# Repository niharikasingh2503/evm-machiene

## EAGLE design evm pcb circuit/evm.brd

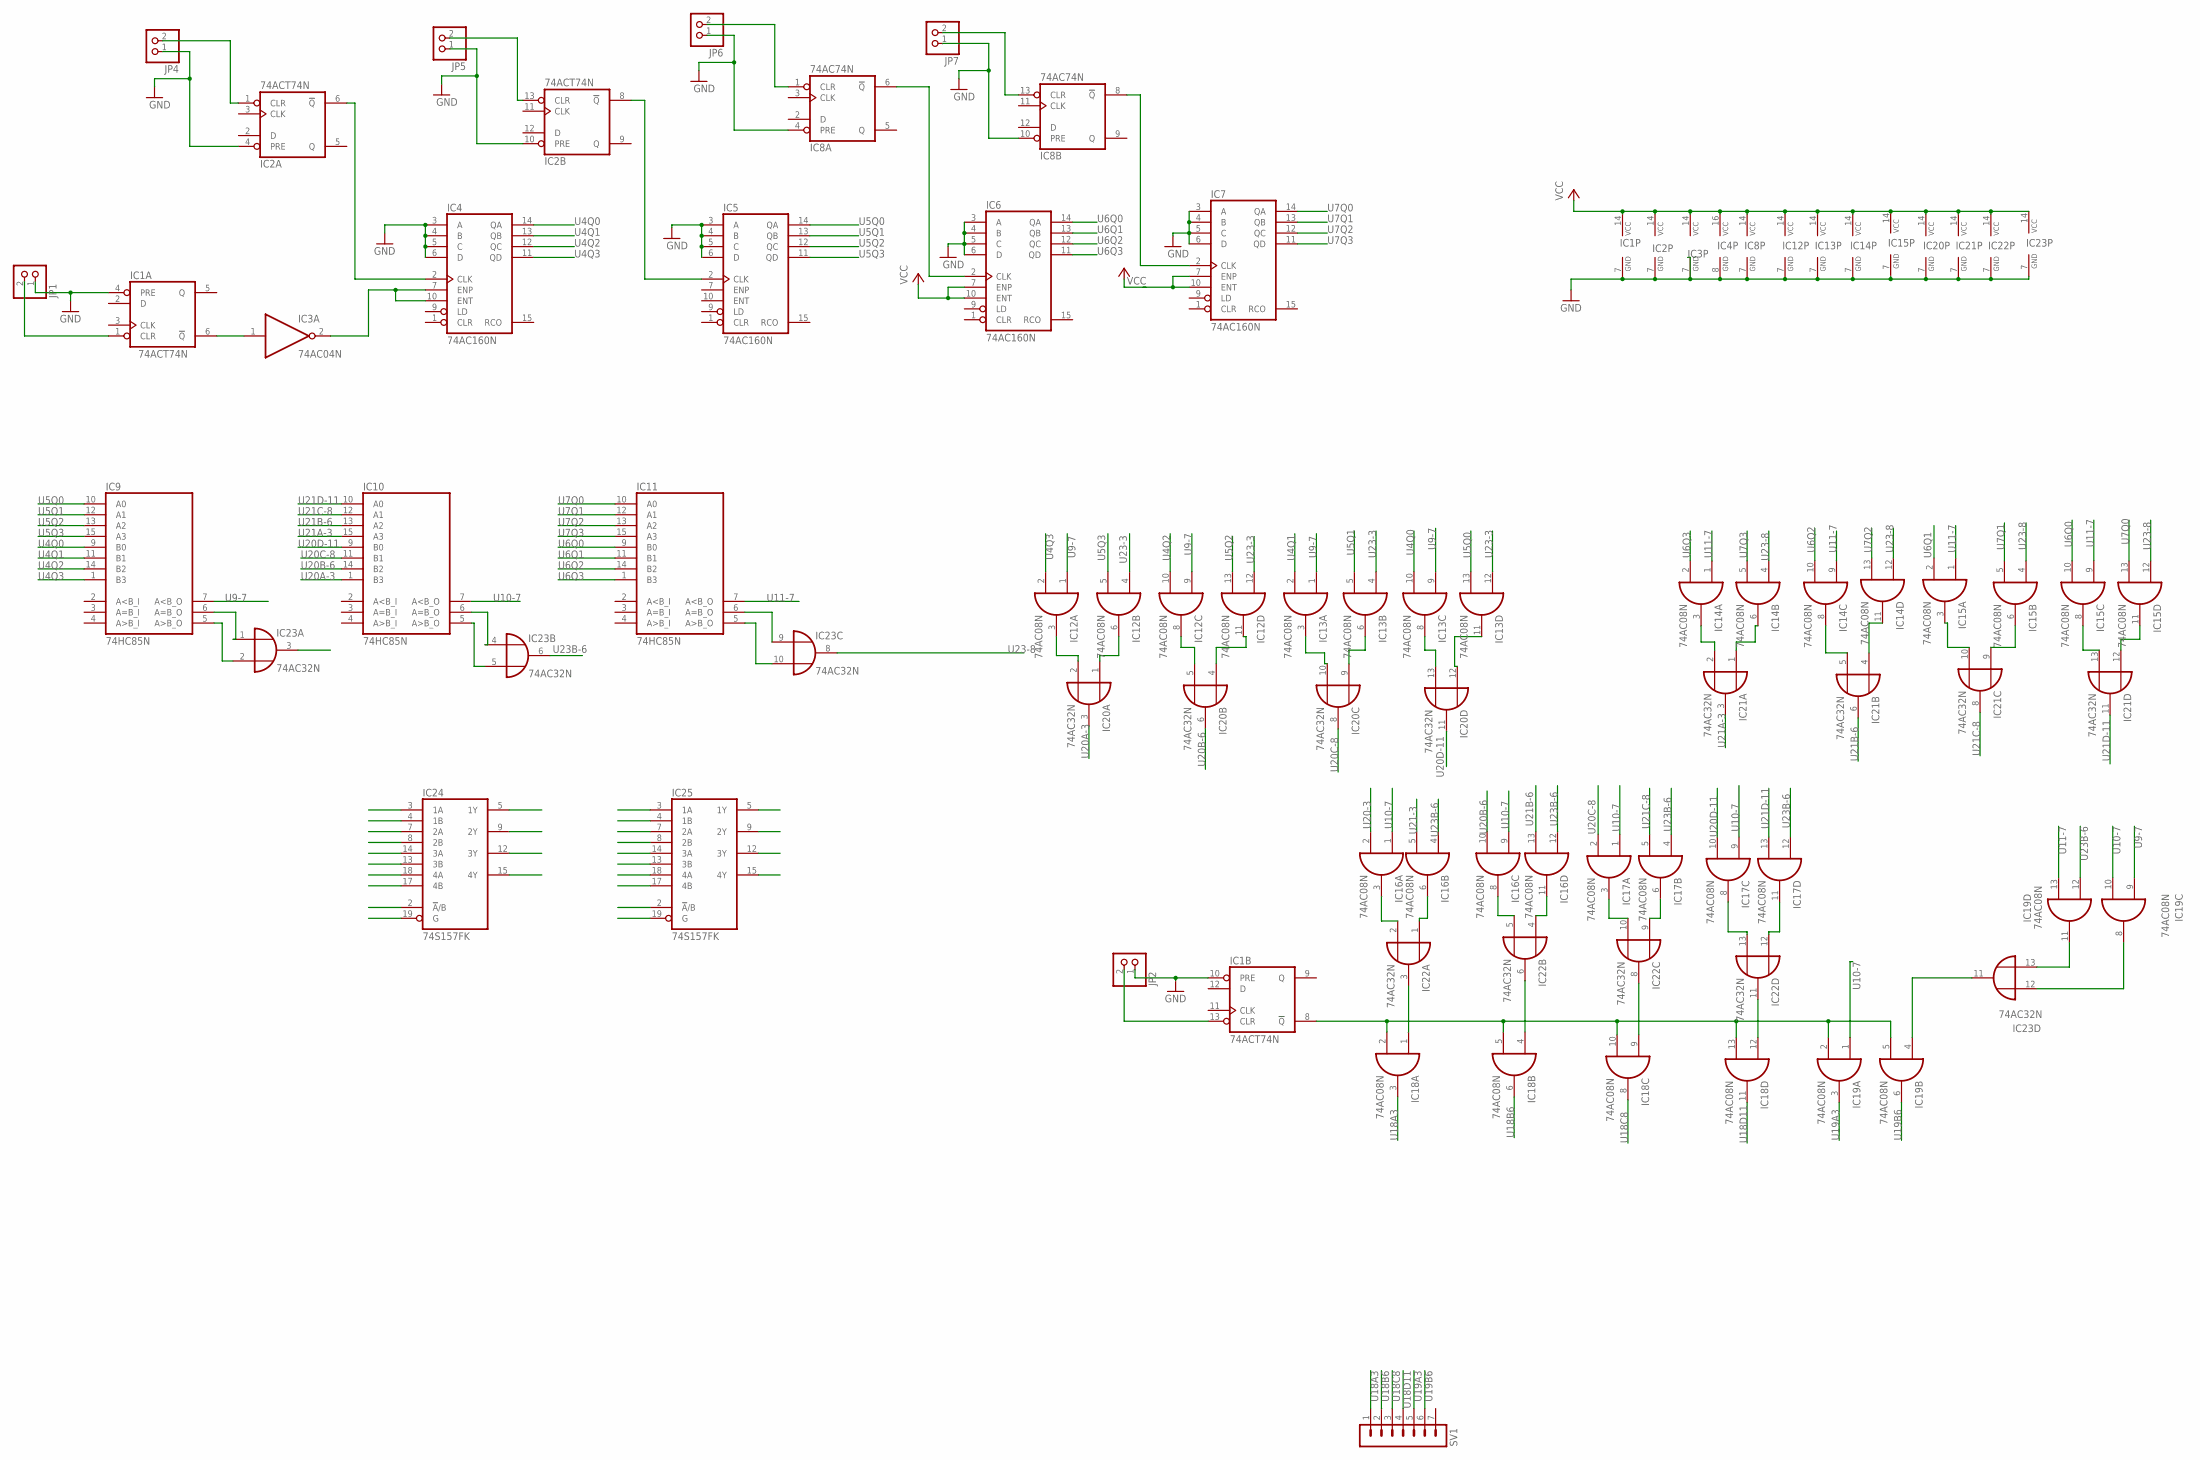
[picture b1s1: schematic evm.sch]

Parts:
IC1, IC2: 74ACT74N; DIL14
IC3: 74AC04N; DIL14
IC4, IC5, IC6, IC7: 74AC160N; DIL16
IC8: 74AC74N; DIL14
IC9, IC10, IC11: 74HC85N; DIL16
IC12, IC13, IC14, IC15, IC16, IC17, IC18, IC19: 74AC08N; DIL14
IC20, IC21, IC22, IC23: 74AC32N; DIL14
IC24, IC25: 74S157FK; LCC20
JP1, JP2, JP4, JP5, JP6, JP7: PINHD-1X2; 1X02
SV1: MA07-1

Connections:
GND: IC1.4 (PRE), IC1.7 (GND), IC1.10 (PRE), IC2.4 (PRE), IC2.7 (GND), IC2.10 (PRE), IC3.7 (GND), IC4.3 (A), IC4.4 (B), IC4.5 (C), IC4.6 (D), IC4.8 (GND), IC5.3 (A), IC5.4 (B), IC5.5 (C), IC5.6 (D), IC5.8 (GND), IC6.3 (A), IC6.4 (B), IC6.5 (C), IC6.6 (D), IC6.8 (GND), IC7.3 (A), IC7.4 (B), IC7.5 (C), IC7.6 (D), IC7.8 (GND), IC8.4 (PRE), IC8.7 (GND), IC8.10 (PRE), IC9.8 (GND), IC10.8 (GND), IC11.8 (GND), IC12.7 (GND), IC13.7 (GND), IC14.7 (GND), IC15.7 (GND), IC16.7 (GND), IC17.7 (GND), IC18.7 (GND), IC19.7 (GND), IC20.7 (GND), IC21.7 (GND), IC22.7 (GND), IC23.7 (GND), JP1.1, JP2.1, JP4.1, JP5.1, JP6.1, JP7.1
unnamed: IC1.13 (CLR), JP2.2
unnamed: IC1.6 (!Q), IC3.1 (I)
unnamed: IC1.1 (CLR), JP1.2
unnamed: IC3.2 (O), IC4.7 (ENP), IC4.10 (ENT)
unnamed: IC2.6 (!Q), IC4.2 (CLK)
unnamed: IC2.1 (CLR), JP4.2
unnamed: IC16.3 (O), IC22.2 (I1)
unnamed: IC18.1 (I0), IC22.3 (O)
unnamed: IC18.4 (I0), IC22.6 (O)
unnamed: IC16.6 (O), IC22.1 (I0)
unnamed: IC2.13 (CLR), JP5.2
unnamed: IC2.8 (!Q), IC5.2 (CLK)
unnamed: IC6.2 (CLK), IC8.6 (!Q)
unnamed: IC8.1 (CLR), JP6.2
unnamed: IC16.8 (O), IC22.5 (I1)
unnamed: IC16.11 (O), IC22.4 (I0)
unnamed: IC17.3 (O), IC22.10 (I1)
unnamed: IC17.6 (O), IC22.9 (I0)
unnamed: IC7.2 (CLK), IC8.8 (!Q)
unnamed: IC8.13 (CLR), JP7.2
unnamed: IC9.6 (A=B_O), IC23.1 (I0)
unnamed: IC12.3 (O), IC20.2 (I1)
unnamed: IC9.5 (A>B_O), IC23.2 (I1)
unnamed: IC11.6 (A=B_O), IC23.9 (I0)
unnamed: IC12.6 (O), IC20.1 (I0)
unnamed: IC12.8 (O), IC20.5 (I1)
unnamed: IC12.11 (O), IC20.4 (I0)
unnamed: IC13.3 (O), IC20.10 (I1)
unnamed: IC13.6 (O), IC20.9 (I0)
unnamed: IC13.8 (O), IC20.13 (I1)
unnamed: IC13.11 (O), IC20.12 (I0)
unnamed: IC14.3 (O), IC21.2 (I1)
unnamed: IC11.5 (A>B_O), IC23.10 (I1)
unnamed: IC14.6 (O), IC21.1 (I0)
unnamed: IC14.8 (O), IC21.5 (I1)
unnamed: IC14.11 (O), IC21.4 (I0)
unnamed: IC15.3 (O), IC21.10 (I1)
unnamed: IC15.6 (O), IC21.9 (I0)
unnamed: IC15.8 (O), IC21.13 (I1)
unnamed: IC15.11 (O), IC21.12 (I0)
unnamed: IC10.6 (A=B_O), IC23.4 (I0)
unnamed: IC17.8 (O), IC22.13 (I1)
unnamed: IC10.5 (A>B_O), IC23.5 (I1)
unnamed: IC17.11 (O), IC22.12 (I0)
unnamed: IC18.12 (I0), IC22.11 (O)
unnamed: IC1.8 (!Q), IC18.2 (I1), IC18.5 (I1), IC18.10 (I1), IC18.13 (I1), IC19.2 (I1), IC19.5 (I1)
unnamed: IC19.4 (I0), IC23.11 (O)
unnamed: IC19.11 (O), IC23.13 (I1)
unnamed: IC19.8 (O), IC23.12 (I0)
unnamed: IC18.9 (I0), IC22.8 (O)
U4Q0: IC4.14 (QA), IC9.9 (B0), IC13.10 (I1)
U4Q1: IC4.13 (QB), IC9.11 (B1), IC13.2 (I1)
U4Q2: IC4.12 (QC), IC9.14 (B2), IC12.10 (I1)
U4Q3: IC4.11 (QD), IC9.1 (B3), IC12.2 (I1)
U5Q0: IC5.14 (QA), IC9.10 (A0), IC13.13 (I1)
U5Q1: IC5.13 (QB), IC9.12 (A1), IC13.5 (I1)
U5Q2: IC5.12 (QC), IC9.13 (A2), IC12.13 (I1)
U5Q3: IC5.11 (QD), IC9.15 (A3), IC12.5 (I1)
U6Q0: IC6.14 (QA), IC11.9 (B0), IC15.10 (I1)
U6Q1: IC6.13 (QB), IC11.11 (B1), IC15.2 (I1)
U6Q2: IC6.12 (QC), IC11.14 (B2), IC14.10 (I1)
U6Q3: IC6.11 (QD), IC11.1 (B3), IC14.2 (I1)
U7Q0: IC7.14 (QA), IC11.10 (A0), IC15.13 (I1)
U7Q1: IC7.13 (QB), IC11.12 (A1), IC15.5 (I1)
U7Q2: IC7.12 (QC), IC11.13 (A2), IC14.13 (I1)
U7Q3: IC7.11 (QD), IC11.15 (A3), IC14.5 (I1)
U9-7: IC9.7 (A<B_O), IC12.1 (I0), IC12.9 (I0), IC13.1 (I0), IC13.9 (I0), IC19.9 (I0)
U10-7: IC10.7 (A<B_O), IC16.1 (I0), IC16.9 (I0), IC17.1 (I0), IC17.9 (I0), IC19.1 (I0), IC19.10 (I1)
U11-7: IC11.7 (A<B_O), IC14.1 (I0), IC14.9 (I0), IC15.1 (I0), IC15.9 (I0), IC19.13 (I1)
U18A3: IC18.3 (O), SV1.1
U18B6: IC18.6 (O), SV1.2
U18C8: IC18.8 (O), SV1.3
U18D11: IC18.11 (O), SV1.4
U19A3: IC19.3 (O), SV1.5
U19B6: IC19.6 (O), SV1.6
U20-3: IC16.2 (I1)
U20A-3: IC10.1 (B3), IC20.3 (O)
U20B-6: IC10.14 (B2), IC16.10 (I1), IC20.6 (O)
U20C-8: IC10.11 (B1), IC17.2 (I1), IC20.8 (O)
U20D-11: IC10.9 (B0), IC17.10 (I1), IC20.11 (O)
U21-3: IC16.5 (I1)
U21A-3: IC10.15 (A3), IC21.3 (O)
U21B-6: IC10.13 (A2), IC16.13 (I1), IC21.6 (O)
U21C-8: IC10.12 (A1), IC17.5 (I1), IC21.8 (O)
U21D-11: IC10.10 (A0), IC17.13 (I1), IC21.11 (O)
U23-3: IC12.4 (I0), IC12.12 (I0), IC13.4 (I0), IC13.12 (I0)
U23-8: IC14.4 (I0), IC14.12 (I0), IC15.4 (I0), IC15.12 (I0), IC23.8 (O)
U23B-6: IC16.4 (I0), IC16.12 (I0), IC17.4 (I0), IC17.12 (I0), IC19.12 (I0), IC23.6 (O)
VCC: IC1.14 (VCC), IC2.14 (VCC), IC3.14 (VCC), IC4.16 (VCC), IC5.16 (VCC), IC6.7 (ENP), IC6.10 (ENT), IC6.16 (VCC), IC7.16 (VCC), IC8.14 (VCC), IC9.16 (VCC), IC10.16 (VCC), IC11.16 (VCC), IC12.14 (VCC), IC13.14 (VCC), IC14.14 (VCC), IC15.14 (VCC), IC16.14 (VCC), IC17.14 (VCC), IC18.14 (VCC), IC19.14 (VCC), IC20.14 (VCC), IC21.14 (VCC), IC22.14 (VCC), IC23.14 (VCC)
VCC1: IC7.7 (ENP), IC7.10 (ENT)

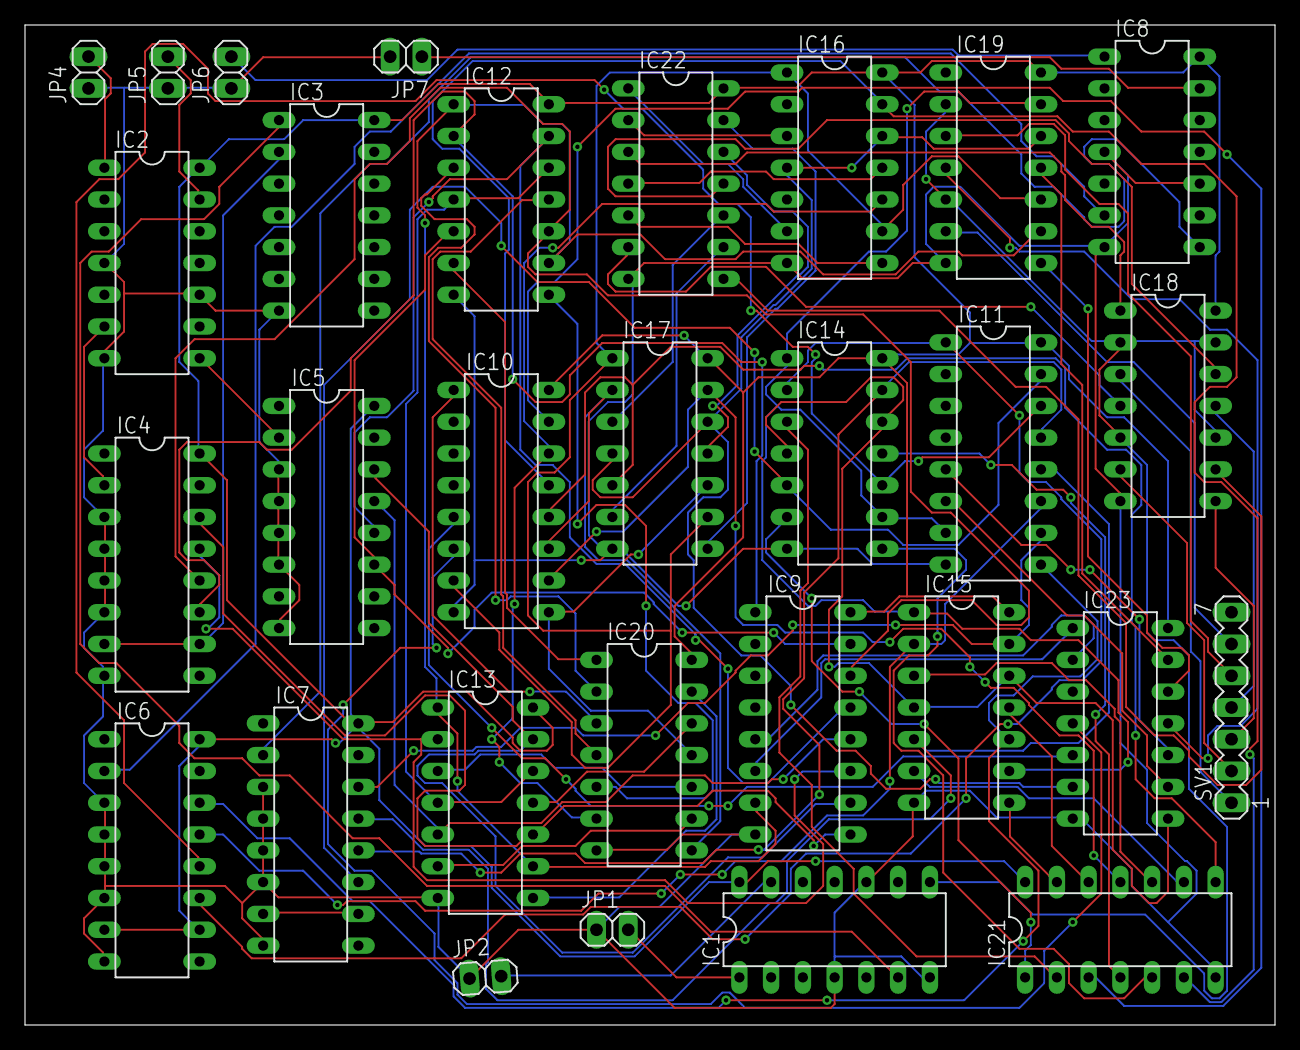
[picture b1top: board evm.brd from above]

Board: 2 copper layers, 100.0 x 80.0 mm, 30 parts (0 on the bottom side), 89 nets.

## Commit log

2023-04-08 Add files via upload
    updated version
